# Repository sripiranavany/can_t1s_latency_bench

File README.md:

# CAN over Ethernet Latency Bench

A testbed for measuring latency when **CAN traffic is tunnelled over automotive
Ethernet**, built on Zephyr RTOS and STM32.

The aim is to quantify what it costs, in latency and jitter, to carry CAN frames
across single-pair Ethernet using IEEE 1722 / [Open1722](https://github.com/COVESA/Open1722)
(AVTP CAN encapsulation), compared with a native CAN bus. The matrix of
configurations to compare:

| | Classic CAN | CAN FD |
| --- | --- | --- |
| **10BASE-T1S** (PLCA multidrop) | Current focus | Planned |
| **100BASE-T1** (point-to-point) | Planned | Planned |

```
 CAN node ──CAN──▶ STM32 (Zephyr) ──SPI──▶ LAN8651 ══10BASE-T1S (PLCA)══ LAN8670 ──USB──▶ Linux host
                   bxCAN + OA-TC6           MAC-PHY                         EVB-LAN8670-USB   timestamps / analysis
```

## Technology stack

| Layer | Choice |
| --- | --- |
| RTOS | Zephyr |
| MCU | STM32 NUCLEO-F439ZI (bxCAN, classic CAN 2.0 only). A CAN FD capable MCU (FDCAN) is needed for the FD tests |
| Ethernet | 10BASE-T1S with PLCA, Microchip LAN8651 (MAC-PHY over SPI, OA TC6). 100BASE-T1 planned |
| CAN transport | IEEE 1722 AVTP via Open1722 |
| CAN PHY | MCP2562FD transceiver, PESD2CAN protection |
| Host | Linux (Raspberry Pi / PC) with EVB-LAN8670-USB, `microchip_t1s` driver |

## Status

| Item | State |
| --- | --- |
| SPI link STM32 ↔ Click Shield verified | Done |
| LAN8651 bring-up on Zephyr (direct wiring and Click Shield socket 3) | Done |
| 10BASE-T1S frames received on STM32 and bridged out on CAN1 | Working prototype (fixed CAN ID `0x123`) |
| Linux host PLCA setup (driver build, hotplug automation) | Done |
| Custom CAN SPE carrier PCB | Schematic and layout in progress |
| Open1722 (AVTP CAN) integration | Not started |
| CAN FD tests | Planned, needs an FDCAN-capable board |
| 100BASE-T1 tests | Planned, needs a 100BASE-T1 PHY / board |
| Latency measurement and analysis | Not started |

## Repository layout

| Path | Contents |
| --- | --- |
| [`host-tools/with-click-shield/`](host-tools/with-click-shield/) | Zephyr firmware for the NUCLEO-F439ZI: LAN8651 bring-up, raw-frame RX, CAN bridge. Wiring variants are selected with devicetree overlays |
| [`host-tools/t1s-plca-setup/`](host-tools/t1s-plca-setup/README.md) | udev rules, systemd unit and scripts that put an EVB-LAN8670-USB into a PLCA-configured state on boot and hotplug |
| [`hardware/CAN SPE CARRIER/`](hardware/CAN%20SPE%20CARRIER/README.md) | KiCad project for the carrier board (CAN transceiver + 10BASE-T1S on a Nucleo-144 / click-shield footprint) |
| [`hardware/kicad-files/`](hardware/kicad-files/) | Third-party KiCad parts (MCP2562FD, PESD2CAN) |
| [`docs/`](docs/) | Bring-up notes, see below |

## Documentation

- [Direct LAN8651 ↔ STM32F439ZI wiring](docs/direct-lan8651-stm32f439zi.md): the known-good hardware setup, plus the Click Shield route
- [SPI verification on the Click Shield](docs/spi-verification-click-shield.md): loopback test and pin mapping
- [10BASE-T1S on Linux](docs/t1s-driver-build.md): building the PHY driver and manual PLCA testing
- [Useful links](docs/links): Click Shield and Nucleo-144 datasheets

## Getting started

Prerequisites: a Zephyr SDK and `west` workspace, a NUCLEO-F439ZI, a MikroE
Two-Wire ETH Click (LAN8651), and a Linux host with an EVB-LAN8670-USB.

1. **Host side.** Build the `microchip_t1s` driver and set up PLCA, following
   [`docs/t1s-driver-build.md`](docs/t1s-driver-build.md) and then
   [`host-tools/t1s-plca-setup`](host-tools/t1s-plca-setup/README.md).
2. **Wire the Click board** to the Nucleo as described in
   [`docs/direct-lan8651-stm32f439zi.md`](docs/direct-lan8651-stm32f439zi.md).
3. **Build and flash the firmware:**

   ```bash
   cd host-tools/with-click-shield
   west build -b nucleo_f439zi -p always .
   west flash
   ```

   To use the Click Shield and/or the CAN bridge, stack overlays:

   ```bash
   west build -b nucleo_f439zi -p always . \
       -DEXTRA_DTC_OVERLAY_FILE="click-shield.overlay;can.overlay"
   ```

   The CAN overlay uses PD0 (RX) / PD1 (TX) and needs an external CAN
   transceiver. See the header of [`can.overlay`](host-tools/with-click-shield/can.overlay).

## Notes

- bxCAN on the STM32F4 is classic CAN 2.0 only (8-byte payload, 1 Mbit/s max). There is no CAN FD on this part, so the CAN FD runs will need a different MCU with FDCAN.
- Click Shield socket 3 needs its logic-level switch set to 3V3.
- `_backup/` holds an older EVB-LAN8670 setup guide kept for reference.

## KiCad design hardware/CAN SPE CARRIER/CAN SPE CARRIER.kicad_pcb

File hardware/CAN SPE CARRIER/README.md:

# CAN SPE CARRIER – PCB Routing Guide (for KiCad beginners)

This file explains **how the board was routed**, **what you are looking at when you open it in KiCad**,
and **what to check before sending it to a manufacturer**.

> **Fixed parts:** J3, J4, J5 and J6 are the click-shield / mainboard headers. Their positions were
> **not allowed to change**, so everything else was placed and routed around them.

---

## 1. Files in this folder

| File | What it is |
|---|---|
| `CAN SPE CARRIER.kicad_pro` | Project file (design rules, net classes) |
| `CAN SPE CARRIER.kicad_sch` | Schematic |
| `CAN SPE CARRIER.kicad_pcb` | The routed board – **open this one** |
| `CAN SPE CARRIER-backups/` | Automatic zip backups. `…-before-routing.kicad_pcb` is your board **before** the re-route |
| `_autosave-*.kicad_pcb` | KiCad autosave, safe to ignore/delete |
| `~*.lck` | Lock files from an earlier session. KiCad may warn "file is open" – if KiCad is not running, click *Ignore/Open anyway* or delete the `.lck` files |

---

## 2. Quick glossary

- **Net** – a set of pads that must be electrically connected (e.g. `GND`, `+3V3`, `/SPI_SCK`).
- **Track / trace** – a copper line that carries a net.
- **Via** – a plated hole that moves a track from one copper layer to the other.
- **Pad** – the copper spot on a part where you solder.
- **Zone / pour** – a big filled copper area (here: ground).
- **Net class** – a group of nets that share rules (track width, clearance). Here: `Default` and `Power`.
- **Ratsnest** – thin straight lines in KiCad showing connections that are *not yet routed*. A finished board has none.
- **DRC** – Design Rule Check; KiCad's automatic error checker.

---

## 3. Why the colours look different in KiCad

KiCad draws each copper layer in its own colour. If you opened the board and everything "changed colour", this is normal:

| Colour (default theme) | Layer | Meaning |
|---|---|---|
| **Red** | `F.Cu` | Front copper (top side) |
| **Green/Blue** | `B.Cu` | Back copper (bottom side) |
| Light red/green haze | GND zones | The ground pour on each layer |
| Yellow lines | `Edge.Cuts` | Board outline |

Tips:
- **Active layer is bright, the other layers are dimmed.** Press `PgUp` / `PgDn`, or click a layer in the
  right-hand *Appearance* panel, and the colours swap emphasis. That is why the board looks different each time.
- *Appearance* panel → **Layers** → *Colour* swatch lets you change any colour.
- **Highlight a net:** press `` ` `` (backtick) or use *Route → Highlight Net* (shortcut `` ` ``)
  and click a track. Everything on that net lights up, and everything else dims. This is the **best way to
  understand the routing**.
- *Appearance* → **Objects** → untick *Zones* (or set *Zone fill* opacity low) to hide the ground pour so you
  can see the tracks clearly.
- *Appearance* → **Nets** lets you show/hide or recolour individual nets.
- Press `B` to refill zones after any change; `Ctrl+B` clears the fill.
- **Show the whole board:** `Home`. **Zoom:** scroll wheel. **Measure:** `Ctrl+Shift+M`.

---

## 4. Board overview

```
                    TOP EDGE  (y ≈ 46…50 mm)
   J5 (left, x≈22)  ─────────────────────────  J6 (right, x≈85)
   click-shield side                              mainboard side
        │   J3 (x≈59, y≈73)    J4 (x≈59, y≈50)    │
        │   TP1 D1 R3 R2 C4  ← 3V3 loads           │
        │   C3  TP2          ← 5V cap              │
        │                                          │
        │   C2 C1  U2 (MCP2562 CAN transceiver)    │
        │                       D2  R1  J2   J1    │
        └──────────── BOTTOM (y ≈ 140 mm) ─────────┘
```

Roughly 69 × 93 mm board, 2 copper layers.

Signal flow in one sentence: **mainboard (J6→J4) and click shield (J5→J3) feed the CAN transceiver U2, whose CANH/CANL
outputs go through the protection diode (D1 / D2) and termination (R1 + J4, R2 + J6) to the screw terminals J1 and J2.**

### 4.1 mikroBUS socket (J3 / J5)

J3 and J5 are the standard **mikroBUS socket**: two 1×8 female headers, 22.86 mm (900 mil) apart, with pin 1 of both
rows at the same end. A click board plugs in directly. No cable and no flipping is needed.

| Row | Pin 1 → pin 8 |
|---|---|
| **J3** (left row) | AN *(not connected)*, RST, CS, SCK, MISO, MOSI, 3V3, GND |
| **J5** (right row) | PWM *(not connected)*, INT, RX *(not connected)*, TX *(not connected)*, SCL, SDA, 5V, GND |

The numbering of J5 runs in the same direction as J3. mikroBUS itself numbers the right-hand pins 16 down to 9, but
that is only a naming convention. Physically PWM sits opposite AN, as on a real click board.

**Connected pins:** RST, CS, SCK, MISO, MOSI, 3V3, GND (J3) and INT, SCL, SDA, 5V, GND (J5). These cover the
**Two-Wire ETH Click (LAN8651)**, which talks to the host over SPI and uses INT and RST. It does not use a UART.

**Not connected:** AN (J3 pin 1) and PWM, RX, TX (J5 pins 1, 3, 4). Their silkscreen labels follow the standard
mikroBUS pin names, but nothing is routed to them. A click board that needs an analog input, a PWM output or a UART
will **not** work in this socket.

---

## 5. Routing, net by net

Track widths: signals **0.25 mm**, power **0.5 mm**, short stubs near pads 0.3 mm.
Clearance everywhere: **0.2 mm**. Vias: **0.6 mm pad / 0.3 mm drill**.

### 5.1 SPI bus (J5 → J3)
| Net | Layer | How |
|---|---|---|
| `/SPI_SCK` | F.Cu (top) | Part of a parallel bundle |
| `/SPI_MISO` | F.Cu (top) | Part of a parallel bundle |
| `/SPI_CS` | F.Cu (top) | Part of a parallel bundle |
| `/SPI_MOSI` | **B.Cu (bottom)** | Runs underneath the bundle |

- The three top-layer signals run side by side using **45° bends** (no sharp 90° corners), keeping the same spacing.
- MOSI was put on the **other layer** so it never has to cross the others → **no vias needed** for SPI.

### 5.2 Mainboard signals (J6 → J4): `/MB_INT`, `/MB_SCL`, `/MB_SDA`
- All on **F.Cu**, running along the **top edge** (above the headers).
- Each one sits at a **different height ("staggered levels")** so the lines never cross each other.
- In KiCad: highlight `/MB_INT` and you will see a long horizontal line at y ≈ 47.2 mm joining J6 to J4.

### 5.3 `/MB_RST`
- On **B.Cu** (bottom). It goes **around the right end of J3** and then up into pin **J3.2**.
- Using the back layer avoids all the top-layer signals.

### 5.4 +3V3 power
- A **0.5 mm trunk on F.Cu** from **J5.16** to **J3.7**, with short branches to the nearby 3.3 V parts
  (R2, R3, D1/LED resistor, C4, TP1).
- **One via** drops the net to **B.Cu**, and a short bottom run feeds **U2** (CAN transceiver VIO) and **C1** (100 nF decoupling).

### 5.5 +5V power
- A **0.5 mm trunk on F.Cu** to **J4.7** and **C3** (5 V bulk cap, placed right beside the trunk).
- A **B.Cu run goes straight down** to **U2** (VCC) and **C2** (100 nF decoupling).
- One via connects the top trunk to the bottom run.

### 5.6 CAN logic: `/CAN_TX`, `/CAN_RX`
- Direct, short **F.Cu** tracks from the J5 header down to U2 (TXD / RXD pins). No vias.

### 5.7 CAN bus: CANH / CANL
The board has two identical CAN pairs, one per screw terminal. Each pair is named in KiCad after its terminal
(no custom label): `Net-(J1-Pin_1)` / `Net-(J1-Pin_2)` (CANH / CANL on J1) and `Net-(J2-Pin_1)` / `Net-(J2-Pin_2)` (J2).
- Each pair is routed **entirely on F.Cu**, with no layer change, so it is suitable for CAN FD tests.
- **Not length-matched, on purpose:** CANH is the outer track and CANL the inner one, so CANH is longer (about 45.3 mm
  against 34.6 mm for CANL, a difference of about 10.7 mm for each pair). The earlier CANL serpentine was removed because CAN
  does not need meanders: the difference is about 70 ps of skew, against a bit time of 200 ns even at 5 Mbit/s in CAN FD.
- **Corners:** there are no 90° corners on the CAN pairs or on the termination links. Every turn is a pair of 45° bends
  (a 1 mm chamfer), which keeps the impedance step small and avoids reflections.
- **Spacing:** the pair runs at 0.25 mm track width and 0.5 mm pitch, apart from where CANH fans out to the ESD diode pad.
- **ESD diodes:** D1 (J1 pair) and D2 (J2 pair) sit in-line on the pair at the corner of the terminal block, about 4 mm
  from the GND pin and about 14 mm of track from pin 1. They cannot go closer because the terminal body covers the area
  below the pins. The diode GND pad has a short trace to a GND via between its two signal pads.
- **Routing:** the pair leaves the transceiver, goes down past the ESD diode and passes under the
  terminal block. It enters the J1 / J2 pins from the south, which is what keeps CANH on the correct side without a via.
- **Termination:** the 120 Ω resistor and its jumper sit next to the pair, with stubs of about 2 mm each
  (R1 + J4 for the J1 pair, R2 + J6 for the J2 pair). The only layer change is the resistor-to-jumper link
  (`Net-(J4-Pin_2)` / `Net-(J6-Pin_2)`), which crosses under the pair on B.Cu through one via.
- **GND stitching vias:** one for each diode GND pad (see above) and four more beside the transceivers at (45.2, 123.9), (50.4, 124.3), (75.2, 123.9) and (80.4, 124.3), so the GND pour pockets enclosed by
  the pair stay connected to the B.Cu pour.

### 5.8 Pull-ups: `/MB_SCL`, `/MB_SDA`, `/MB_INT`, `/MB_RST`
The carrier acts as the mikroBUS socket (host side), so it provides the pull-ups. All four go to **+3V3**:

| Part | Value | Net | Why |
|---|---|---|---|
| R5 | 4.7 kΩ | `/MB_SCL` | I²C clock (open-drain) |
| R6 | 4.7 kΩ | `/MB_SDA` | I²C data (open-drain) |
| R7 | 10 kΩ | `/MB_INT` | Interrupt from the click board (open-drain, active low) |
| R8 | 10 kΩ | `/MB_RST` | Keeps reset released while nothing drives it |

- **Schematic:** the four resistors are at the bottom of the sheet, each with a `+3V3` label on one pin and the net label on the other.
- **PCB:** R5–R7 sit just west of the via column at x ≈ 64 mm / y ≈ 69–74 mm, where `/MB_INT`, `/MB_SCL` and `/MB_SDA` come up to F.Cu. Each has a 1.5 mm stub from its via. A short +3V3 rail at x = 59.2 mm joins the +3V3 trunk at y = 80 mm.
- R8 sits below them. `/MB_RST` runs on B.Cu there, so one extra via at (64.8, 75.1) brings it to F.Cu for R8.
- **Silkscreen:** the value text is hidden on R5–R8 and their reference designators are on the F.Fab layer, because the 2.5 mm spacing leaves no room for silkscreen text.
- If the Nucleo or the click board already has pull-ups on these lines, the extra ones are harmless (4.7 kΩ in parallel is about 2.35 kΩ). Remove R5–R8 only if the combined value would be too strong for your bus speed.

### 5.9 Orientation marks (silkscreen)
The board is a symmetric rectangle with two 2×35 sockets, so it could be plugged onto the Nucleo rotated by 180°. That would put
5 V / 3.3 V on the wrong pins. To prevent this, both silkscreen layers carry orientation text:

| Mark | Where | Meaning |
|---|---|---|
| ▲ + `NUCLEO ST-LINK USB END` | top edge, centred (y ≈ 47–50 mm) | This end goes over the Nucleo's ST-LINK USB connector. Pin 1 of J7 and J8 is here. |
| `NUCLEO ETH / USB END` | bottom edge, centred (y ≈ 139 mm), bottom silk only | This end goes over the Nucleo's RJ45 Ethernet connector and user USB. The screw terminals J1 and J2 are on this side. |
| `J7 PIN 1` / `J8 PIN 1` with arrows | next to the top corners | The arrow points at pin 1 of each 2×35 socket. |

- The texts are on **both** `F.SilkS` and `B.SilkS`. The bottom text is mirrored so it reads correctly when you flip the board over.
  The `NUCLEO ETH / USB END` text is bottom-only, because the top side of that end is covered by the terminal block silkscreen.
- **How the ends were determined:** from the Nucleo 3D model (`NUCLEO-F439ZI-carrier-aligned.step`). The ST-LINK USB connector (CN1)
  is at one end of the Nucleo and the RJ45 at the other. The carrier's pin-1 end (y ≈ 50 mm) is over the ST-LINK end. Please confirm this
  once against the real board before ordering.

### 5.10 Ground (GND)
- A **ground pour (zone) on both F.Cu and B.Cu** covering the whole board.
- Every GND pad connects into the pour (thermal-relief spokes: 0.4 mm bridges, 0.3 mm gap).
- **Vias join the top and bottom pours** so both are one ground. (The board has 23 GND vias: two at the ESD diodes, four near the CAN transceivers and 17 stitching vias spread over the board so no point on the pour is more than about 12 mm from a via – see §8.)
- Because of the pour, you do not see individual GND tracks; ground is "everywhere there is no other signal".

### 5.11 Test points
All eleven test points (TP1 to TP11) are through-hole parts for scope probing (footprint `TestPoint_THTPad_D2.0mm_Drill1.0mm`: 2.0 mm pad, 1.0 mm hole).
Each one sits on a short 0.25 mm stub (2.5 to 4.5 mm; 9 mm for TP4) off its net, in free copper and outside every part's courtyard, so it adds no 90° corners to the CAN pairs.

| Ref | Net | Position (mm) |
|---|---|---|
| TP1 | +3V3 | (48.9, 74.7) |
| TP2 | GND | (57.3, 89.3) |
| TP3 | CANH, J1 pair (`Net-(J1-Pin_1)`) | (80.0, 121.5) |
| TP4 | CANL, J1 pair (`Net-(J1-Pin_2)`) | (70.5, 126.6) |
| TP5 | CANH, J2 pair (`Net-(J2-Pin_1)`) | (52.8, 132.0) |
| TP6 | CANL, J2 pair (`Net-(J2-Pin_2)`) | (44.8, 122.2) |
| TP7 | `/CAN2_TX` (U1 TXD) | (80.0, 75.7) |
| TP8 | `/CAN2_RX` (U1 RXD) | (67.1, 115.6) |
| TP9 | `/CAN1_TX` (U2 TXD) | (27.0, 120.2) |
| TP10 | `/CAN1_RX` (U2 RXD) | (28.0, 124.2) |
| TP11 | +5V | (39.5, 85.4) |

The Two-Wire ETH Click plugs into J3/J5 and covers roughly x = -5 to 58 mm, y = 90 to 118 mm, so the test points were placed outside that area to stay reachable with the module fitted (TP2 sits right at its upper corner).

TP1 and TP2 were first 1.5 mm surface pads. They were moved a few millimetres and converted to the same through-hole footprint,
because the back-layer tracks under their old positions would have clashed with a through-hole pad. TP2 is the scope ground.

---

## 6. Parts that were moved (none of J3–J6)

R1, R2, R3, C1, C3, C4, D1, D2, J2, TP1, TP2.

Why:
- **3.3 V loads** (R2, R3, C4, D1, C1) were moved next to the 3V3 trunk → shorter, simpler power tracks.
- **5 V cap** (C3) moved beside the 5V trunk.
- **D2, R1, J2** were moved **below J1**, because the body of the J1 screw terminal covered their old position.
- ⚠ **Check:** if the wires enter J1 from the **top** side, make sure D2, R1 and J2 don't block the wire entry.

---

## 7. Other changes made
- Added a **`Power` net class** in the project: **0.5 mm** tracks for `+5V` and `+3V3`
  (Board Setup → Design Rules → Net Classes).
- Old routing removed (it had 5 warnings, 8 unconnected items, dangling B.Cu tracks with no vias,
  long diagonal runs and no ground pour) and re-routed from scratch.
- Previous board saved as `CAN SPE CARRIER-backups/CAN SPE CARRIER-before-routing.kicad_pcb`
  (use *File → Restore Local Backup…* or just open that file).

---

## 8. How to review it yourself (step by step)

1. Open `CAN SPE CARRIER.kicad_pcb` (from the project, via the PCB Editor).
2. Press `B` to refill zones.
3. Run **Inspect → Design Rules Checker → Run DRC**. Expected: 0 errors, 0 unconnected items.
   (Tick *"Test for parity between PCB and schematic"* too.)
4. Walk through the nets: press `` ` `` on each track and read the list in §5.
5. Use **View → 3D Viewer** (`Alt+3`) to check that parts don't collide with J1.
6. Use *Appearance → Layers* to view only `F.Cu`, then only `B.Cu`.

### Things to improve / double-check
- **Stitching vias:** 17 GND stitching vias were added in open copper (0.6 / 0.3 mm, at least 0.5 mm from any other net),
  spaced about 12 mm apart or less. Refill the zones (`B`) and re-run DRC after moving any signal track near them.
- **Check the current rating:** 0.5 mm copper at 1 oz handles roughly 1 A; verify this is enough for your 3V3 and 5V loads.
- **Fab capabilities:** the design uses 0.2 mm clearance, 0.25 mm signal tracks and 0.6/0.3 mm vias.
  Confirm your manufacturer allows these (most standard 2-layer services do).
- **Lock files:** delete `~*.lck` if KiCad keeps warning you.

---

## 9. Handy KiCad shortcuts (PCB Editor)

| Key | Action |
|---|---|
| `` ` `` | Highlight net under cursor |
| `B` | Refill all zones |
| `X` | Start routing a track |
| `V` | Place a via while routing (also switches layer) |
| `D` | Drag a track |
| `M` / `G` | Move / Grab (keeps connections) |
| `Del` | Delete selected |
| `Ctrl+Z` | Undo |
| `PgUp/PgDn` | Switch active copper layer |
| `Alt+3` | 3D viewer |
| `Ctrl+Shift+M` | Measure tool |
| `Home` | Zoom to fit |

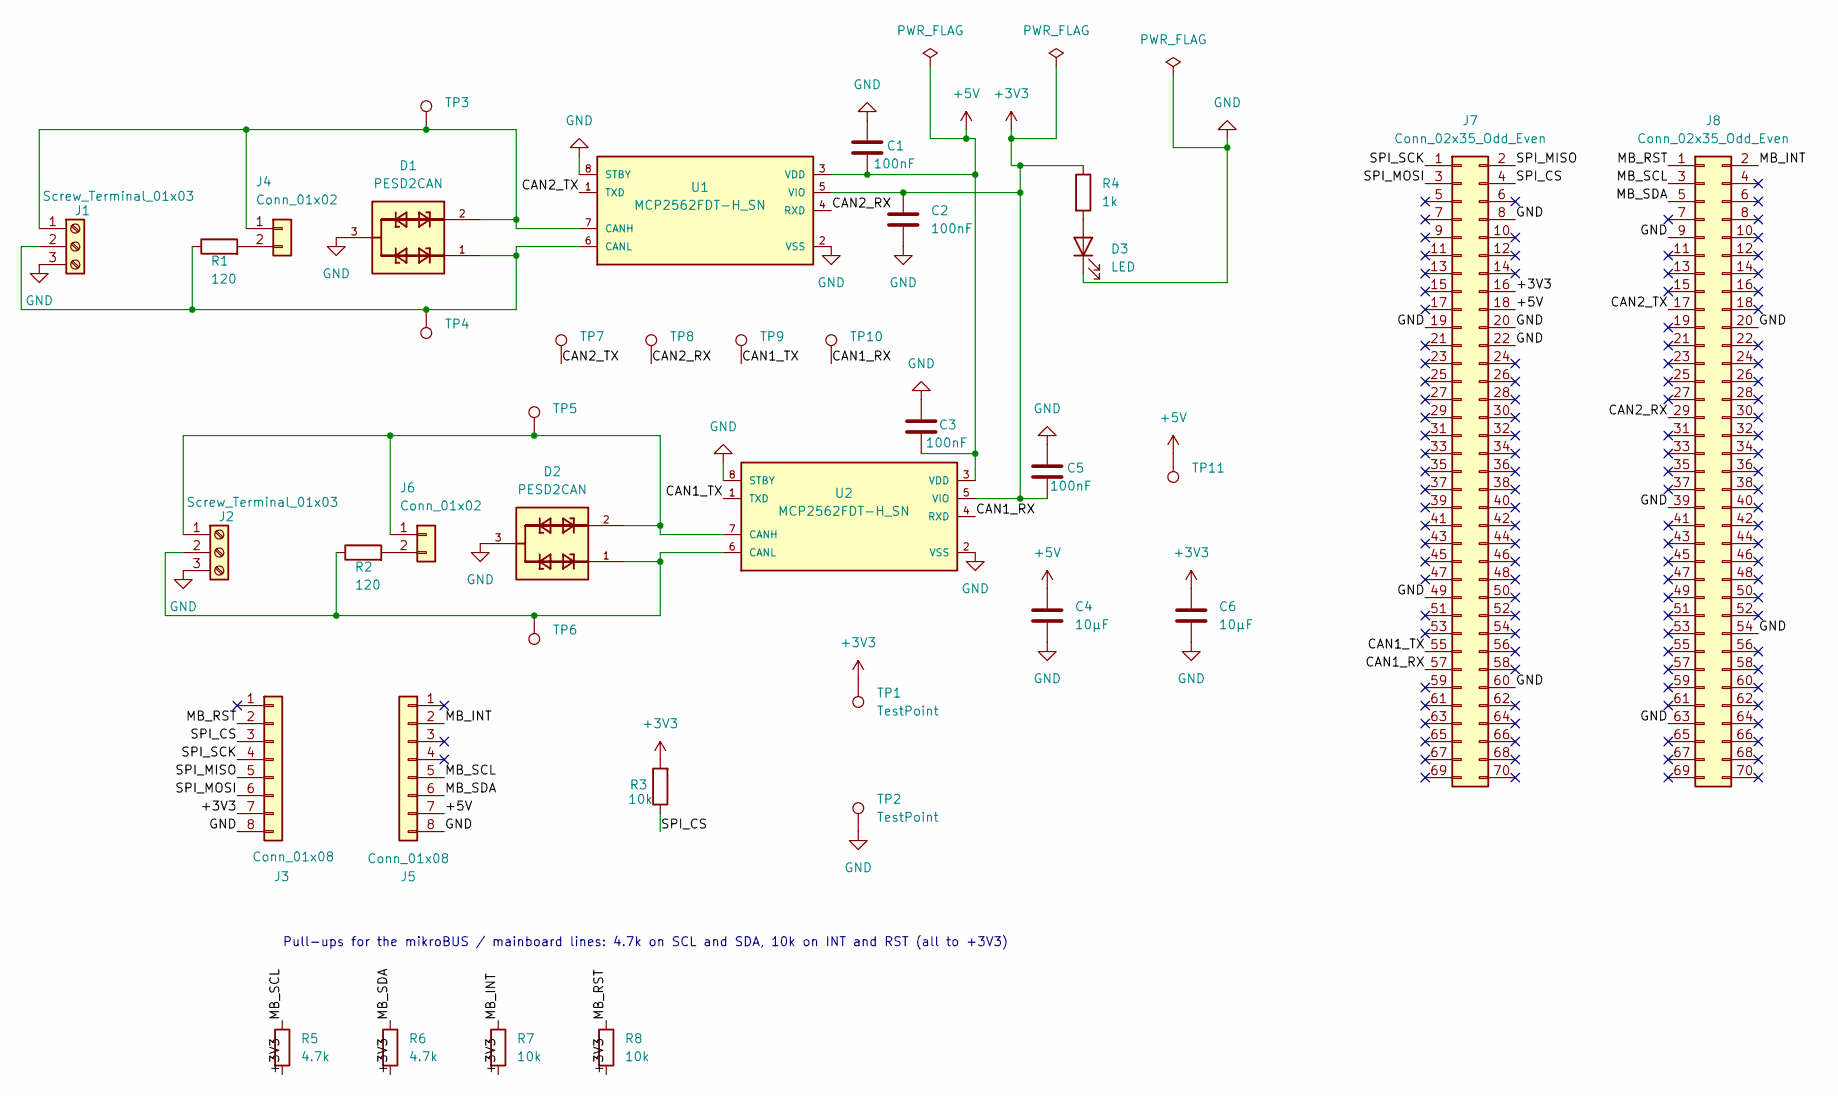
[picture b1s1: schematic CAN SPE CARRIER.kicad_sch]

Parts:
C1, C2, C3, C5: 100nF; C_0805_2012Metric
C4, C6: 10µF; C_0805_2012Metric
D1, D2: PESD2CAN; SOT-23
D3: LED; LED_0805_2012Metric
J1, J2: Screw_Terminal_01x03; TerminalBlock_Phoenix_MKDS-1,5-3-5.08_1x03_P5.08mm_Horizont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
J3, J5: Conn_01x08; PinSocket_1x08_P2.54mm_Vertical
J4, J6: Conn_01x02; PinHeader_1x02_P2.54mm_Vertical
J7, J8: Conn_02x35_Odd_Even; PinSocket_2x35_P2.54mm_Vertical
R1, R2: 120; R_0805_2012Metric
R3, R7, R8: 10k; R_0805_2012Metric
R4: 1k; R_0805_2012Metric
R5, R6: 4.7k; R_0805_2012Metric
TP1, TP2, TP3, TP4, TP5, TP6, TP7, TP8, TP9, TP10, TP11: TestPoint; TestPoint_THTPad_D2.0mm_Drill1.0mm
U1, U2: MCP2562FDT-H_SN; SOIC-8_3.9x4.9mm_P1.27mm

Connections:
+3V3: C2.1, C5.1, C6.1, J3.7, J7.16, R3.2, R4.1, R5.2, R6.2, R7.2, R8.2, TP1.1 (1_1), U1.5 (VIO), U2.5 (VIO)
+5V: C1.1, C3.1, C4.1, J5.7, J7.18, TP11.1 (1_1), U1.3 (VDD), U2.3 (VDD)
/CAN1_RX: J7.57, TP10.1 (1_1), U2.4 (RXD)
/CAN1_TX: J7.55, TP9.1 (1_1), U2.1 (TXD)
/CAN2_RX: J8.29, TP8.1 (1_1), U1.4 (RXD)
/CAN2_TX: J8.17, TP7.1 (1_1), U1.1 (TXD)
/MB_INT: J5.2, J8.2, R7.1
/MB_RST: J3.2, J8.1, R8.1
/MB_SCL: J5.5, J8.3, R5.1
/MB_SDA: J5.6, J8.5, R6.1
/SPI_CS: J3.3, J7.4, R3.1
/SPI_MISO: J3.5, J7.2
/SPI_MOSI: J3.6, J7.3
/SPI_SCK: J3.4, J7.1
GND: C1.2, C2.2, C3.2, C4.2, C5.2, C6.2, D1.3, D2.3, D3.1 (K), J1.3, J2.3, J3.8, J5.8, J7.8, J7.19, J7.20, J7.22, J7.49, J7.60, J8.9, J8.20, J8.39, J8.54, J8.63, TP2.1 (1_1), U1.2 (VSS), U1.8 (STBY), U2.2 (VSS), U2.8 (STBY)
unnamed: D3.2 (A), R4.2
unnamed: D1.2, J1.1, J4.1, TP3.1 (1_1), U1.7 (CANH)
unnamed: D1.1, J1.2, R1.1, TP4.1 (1_1), U1.6 (CANL)
unnamed: D2.2, J2.1, J6.1, TP5.1 (1_1), U2.7 (CANH)
unnamed: D2.1, J2.2, R2.1, TP6.1 (1_1), U2.6 (CANL)
unnamed: J4.2, R1.2
unnamed: J6.2, R2.2

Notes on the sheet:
Pull-ups for the mikroBUS / mainboard lines: 4.7k on SCL and SDA, 10k on INT and RST (all to +3V3)

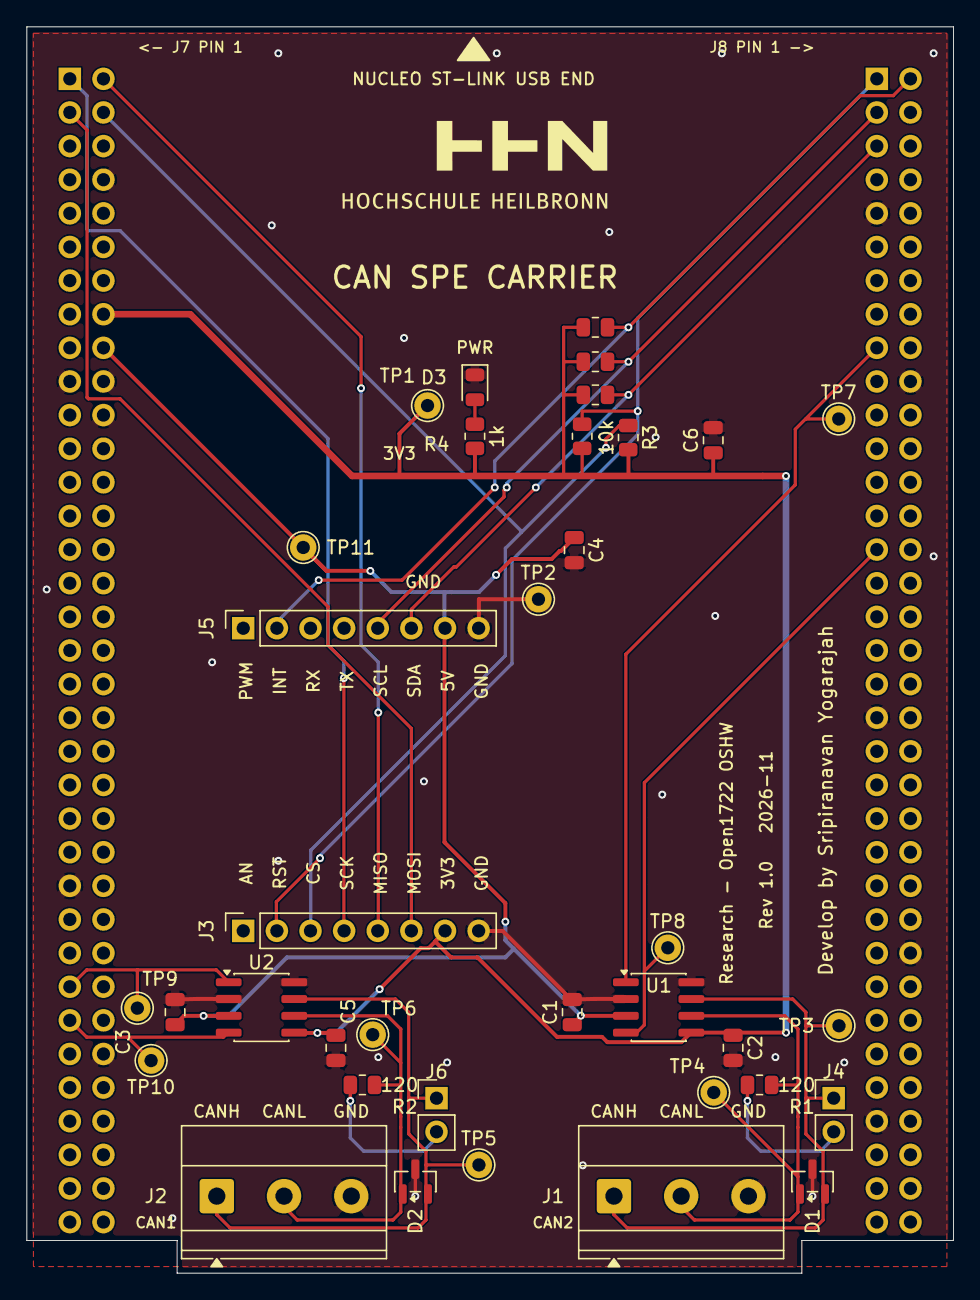
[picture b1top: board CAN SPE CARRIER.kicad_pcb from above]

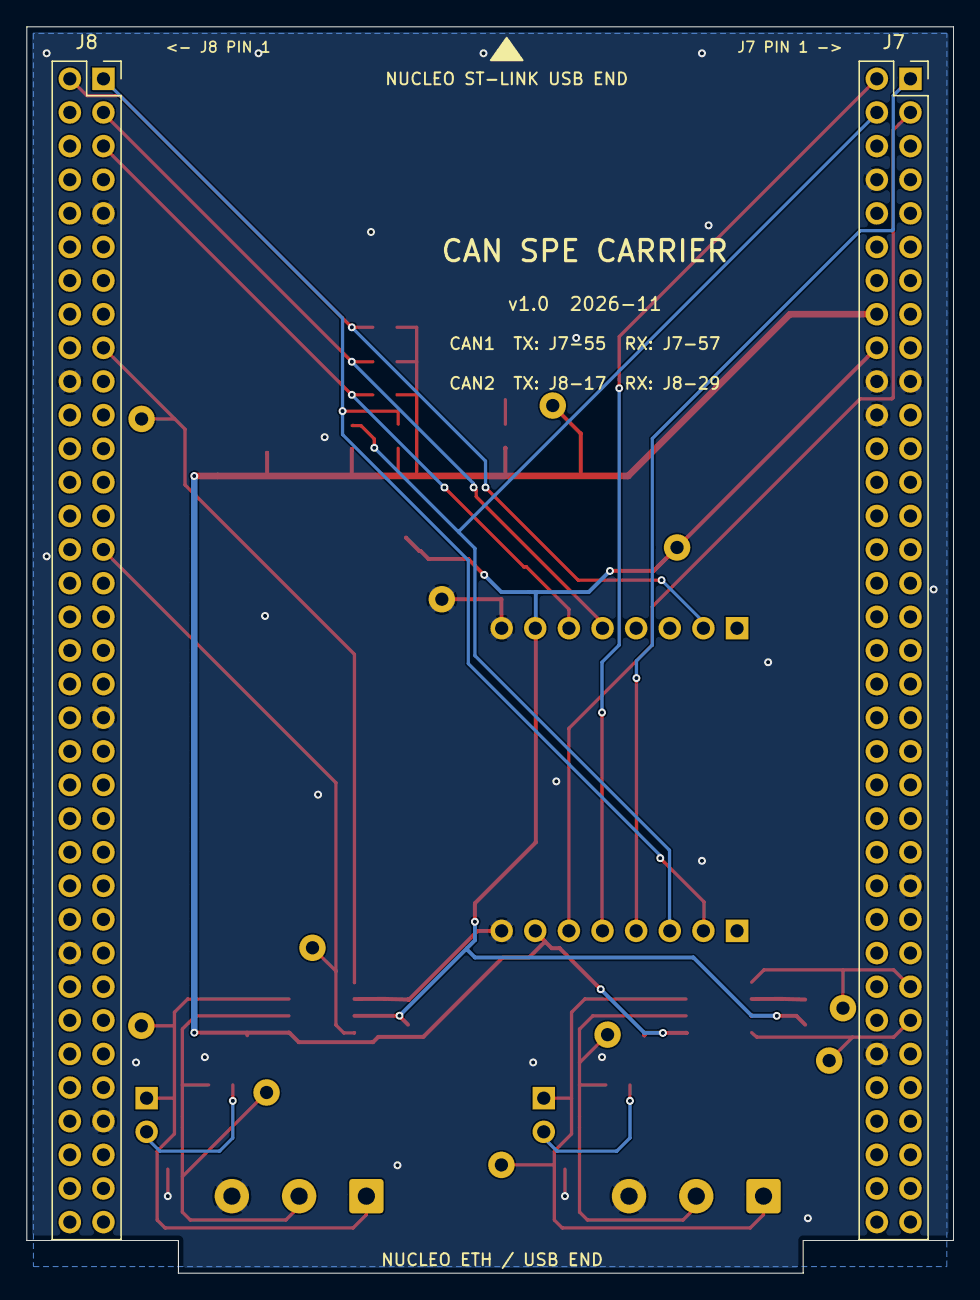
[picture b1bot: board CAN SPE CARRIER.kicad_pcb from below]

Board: 2 copper layers, 70.0 x 94.2 mm, 41 parts (2 on the bottom side), 22 nets.

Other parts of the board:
LOGO1: HHN_Logo_20mm
MECH1: NUCLEO-F439ZI 3D; NUCLEO-F439ZI_3D_Reference
MECH2: Two-Wire ETH Click 3D; TwoWireETH_Click_3D_Reference
